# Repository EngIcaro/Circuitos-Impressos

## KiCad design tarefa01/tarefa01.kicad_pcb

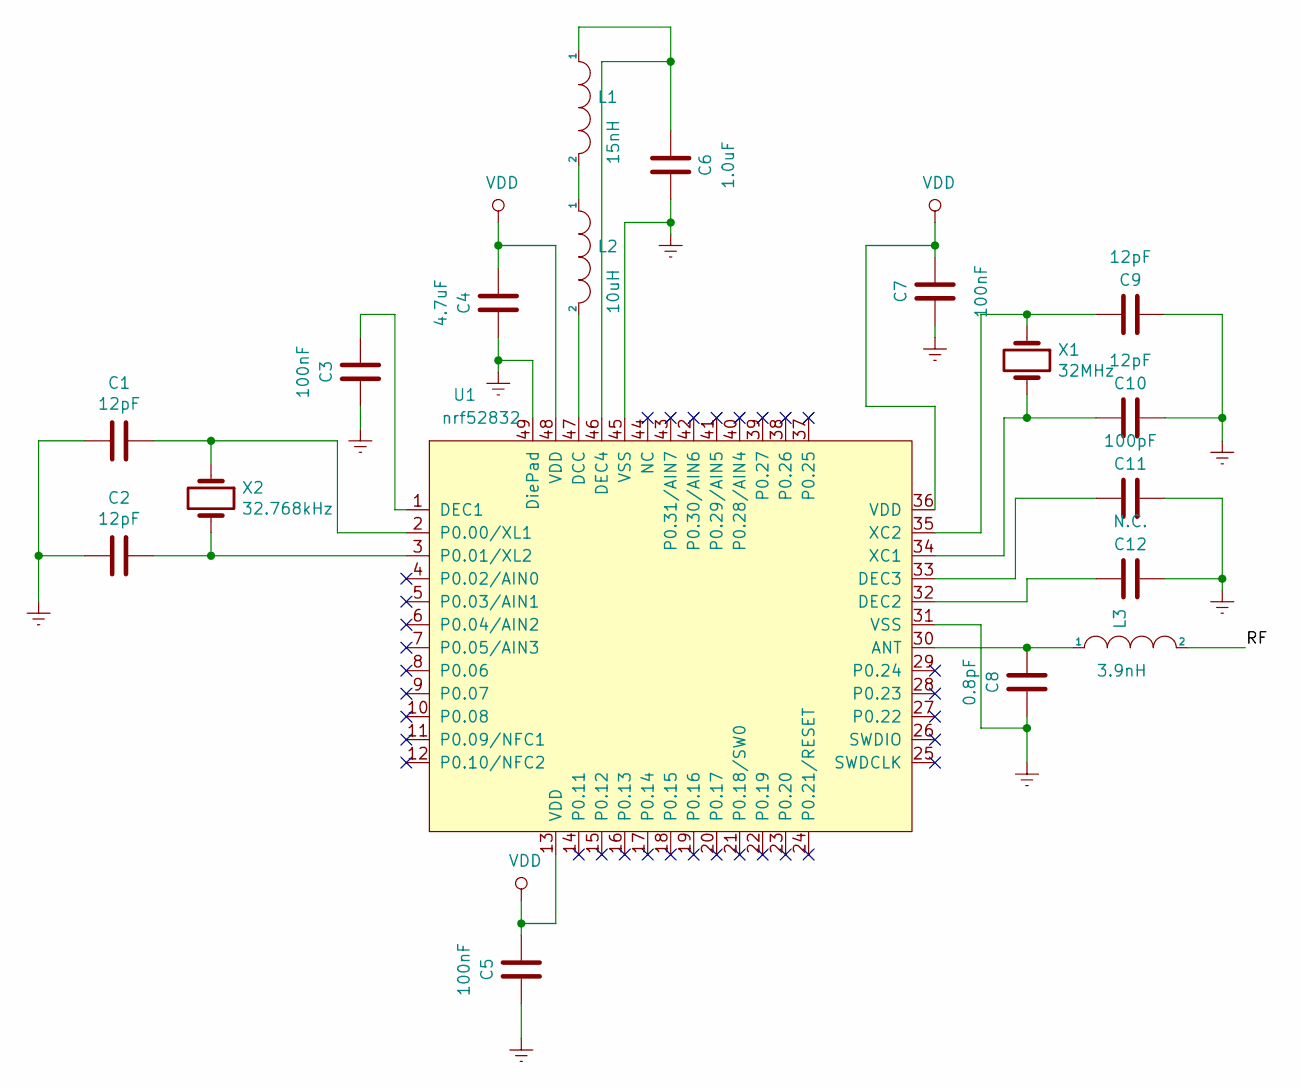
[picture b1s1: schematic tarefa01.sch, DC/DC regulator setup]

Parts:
C1, C2, C9, C10: 12pF; C_0201_0603Metric
C3, C5, C7: 100nF; C_0201_0603Metric
C4: 4.7uF; C_0603_1608Metric_Pad1.05x0.95mm_HandSolder
C6: 1.0uF; C_0402_1005Metric
C8: 0.8pF; C_0201_0603Metric
C11: 100pF; C_0201_0603Metric
C12: N.C.; C_0201_0603Metric
L1: 15nH; L_0402_1005Metric
L2: 10uH; L_0603_1608Metric_Pad1.05x0.95mm_HandSolder
L3: 3.9nH; L_0201_0603Metric
U1: nrf52832; QFN-48_EP_6x6_Pitch0.4mm
X1: 32MHz; Crystal_SMD_2016-4Pin_2.0x1.6mm
X2: 32.768kHz; Crystal_SMD_2012-2Pin_2.0x1.2mm_HandSoldering

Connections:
/RF: L3.2
Earth: C1.2, C2.2, C3.1, C4.1, C5.1, C6.1, C7.1, C8.1, C9.2, C10.2, C11.2, C12.2, U1.31 (VSS), U1.45 (VSS), U1.49 (DiePad)
unnamed: C1.1, U1.2 (P0.00/XL1), X2.1
unnamed: C2.1, U1.3 (P0.01/XL2), X2.2
unnamed: C3.2, U1.1 (DEC1)
unnamed: C6.2, L1.1, U1.46 (DEC4)
unnamed: C8.2, L3.1, U1.30 (ANT)
unnamed: C9.1, U1.35 (XC2), X1.1
unnamed: C10.1, U1.34 (XC1), X1.2
unnamed: C11.1, U1.33 (DEC3)
unnamed: C12.1, U1.32 (DEC2)
unnamed: L1.2, L2.1
unnamed: L2.2, U1.47 (DCC)
VDD: C4.2, C5.2, C7.2, U1.13 (VDD), U1.36 (VDD), U1.48 (VDD)

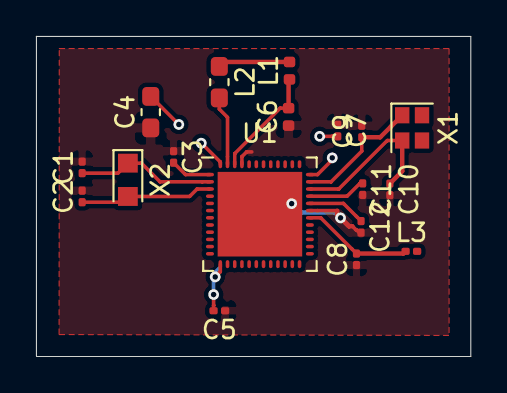
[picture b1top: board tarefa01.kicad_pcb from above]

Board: 2 copper layers, 24.1 x 17.8 mm, 18 parts (0 on the bottom side), 13 nets.

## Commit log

2019-06-03 add footprint
2019-06-04 Resolvendo erros do esquemático
2019-06-05 Resolvendo erro do RF
2019-06-10 Layout em andamento
2019-06-11 adicionando ground plane
2019-06-11 adicionando vdd plane
2019-06-12 Projeto finalizado
